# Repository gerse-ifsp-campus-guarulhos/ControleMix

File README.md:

# **ControleMix**

O Controle Mix é uma placa dedicada para a construção, desenvolvimento e prototipagem de robôs autônomos ou controlado, o foco dela é para robôs voltados a competição (mas isso não impede que a mesma seja usada em outros robôs ou em outras aplicações )

## **Circuito**
 
O circuito leva o [STM32F103C8T6](https://www.st.com/content/ccc/resource/technical/document/reference_manual/59/b9/ba/7f/11/af/43/d5/CD00171190.pdf/files/CD00171190.pdf/jcr:content/translations/en.CD00171190.pdf
) na plataforma  [Blue pill](https://www.techshopbd.com/uploads/product_document/STM32bluepillarduinoguide(1).pdf) a mesma dispõe de entradas e saídas e interfaces de comunicação serial , a ideia principal é universalizar os projetos e principalmente facilitar o projeto elétrico de forma que o desenvolvimento seja mais voltado para a programação. O circuito foi desenvolvido no Kicad e está projetado para fabricação manufatura ([consulte o GERBER](./DOC/GERBER/)), Para mais informações da placa consulte o [esquema elétrico](./DOC/ControleMix.pdf), O circuito contém:

* 10 entradas analogicas de 12 bits com divisor de tensão - 0V a 30V

* 4 saídas acoplada por um [ULN2803A](https://www.st.com/en/interfaces-and-transceivers/uln2803a.html)   (todas PWM)

* 4 Entradas acoplada por um  [ULN2803A](https://www.st.com/en/interfaces-and-transceivers/uln2803a.html)   (todas PWM)

* Serial USART1

* Serial USART3 / I2C2

* Serial USB / CAN

* Conector para mix de sinal do controle RF de até 6 canais

## **Notas para instalação e manipulação nos projetos:**

* sempre consulte o [esquema elétrico](./DOC/ControleMix.pdf).

* Ela tem aproximadamente 60mm por 60mm e contém 2 furos de fixação excêntrico e assimétricos.

* Aconselha se a utilizar de forma que o circuito não fique exposto, ela é utiliza  conectores [molex de passo 1.27mm](
https://www.molex.com/molex/news/display_news.jsp?channel=New&channelId=0&oid=941
)

* Os resistores do divisor de divisão de tensão e os resistores de pull up são array de resistores embora pode ser facilmente substituídos por resistores comuns

* Para desenho do projeto em [3D](./DOC/3D/) consulte o D do circuito

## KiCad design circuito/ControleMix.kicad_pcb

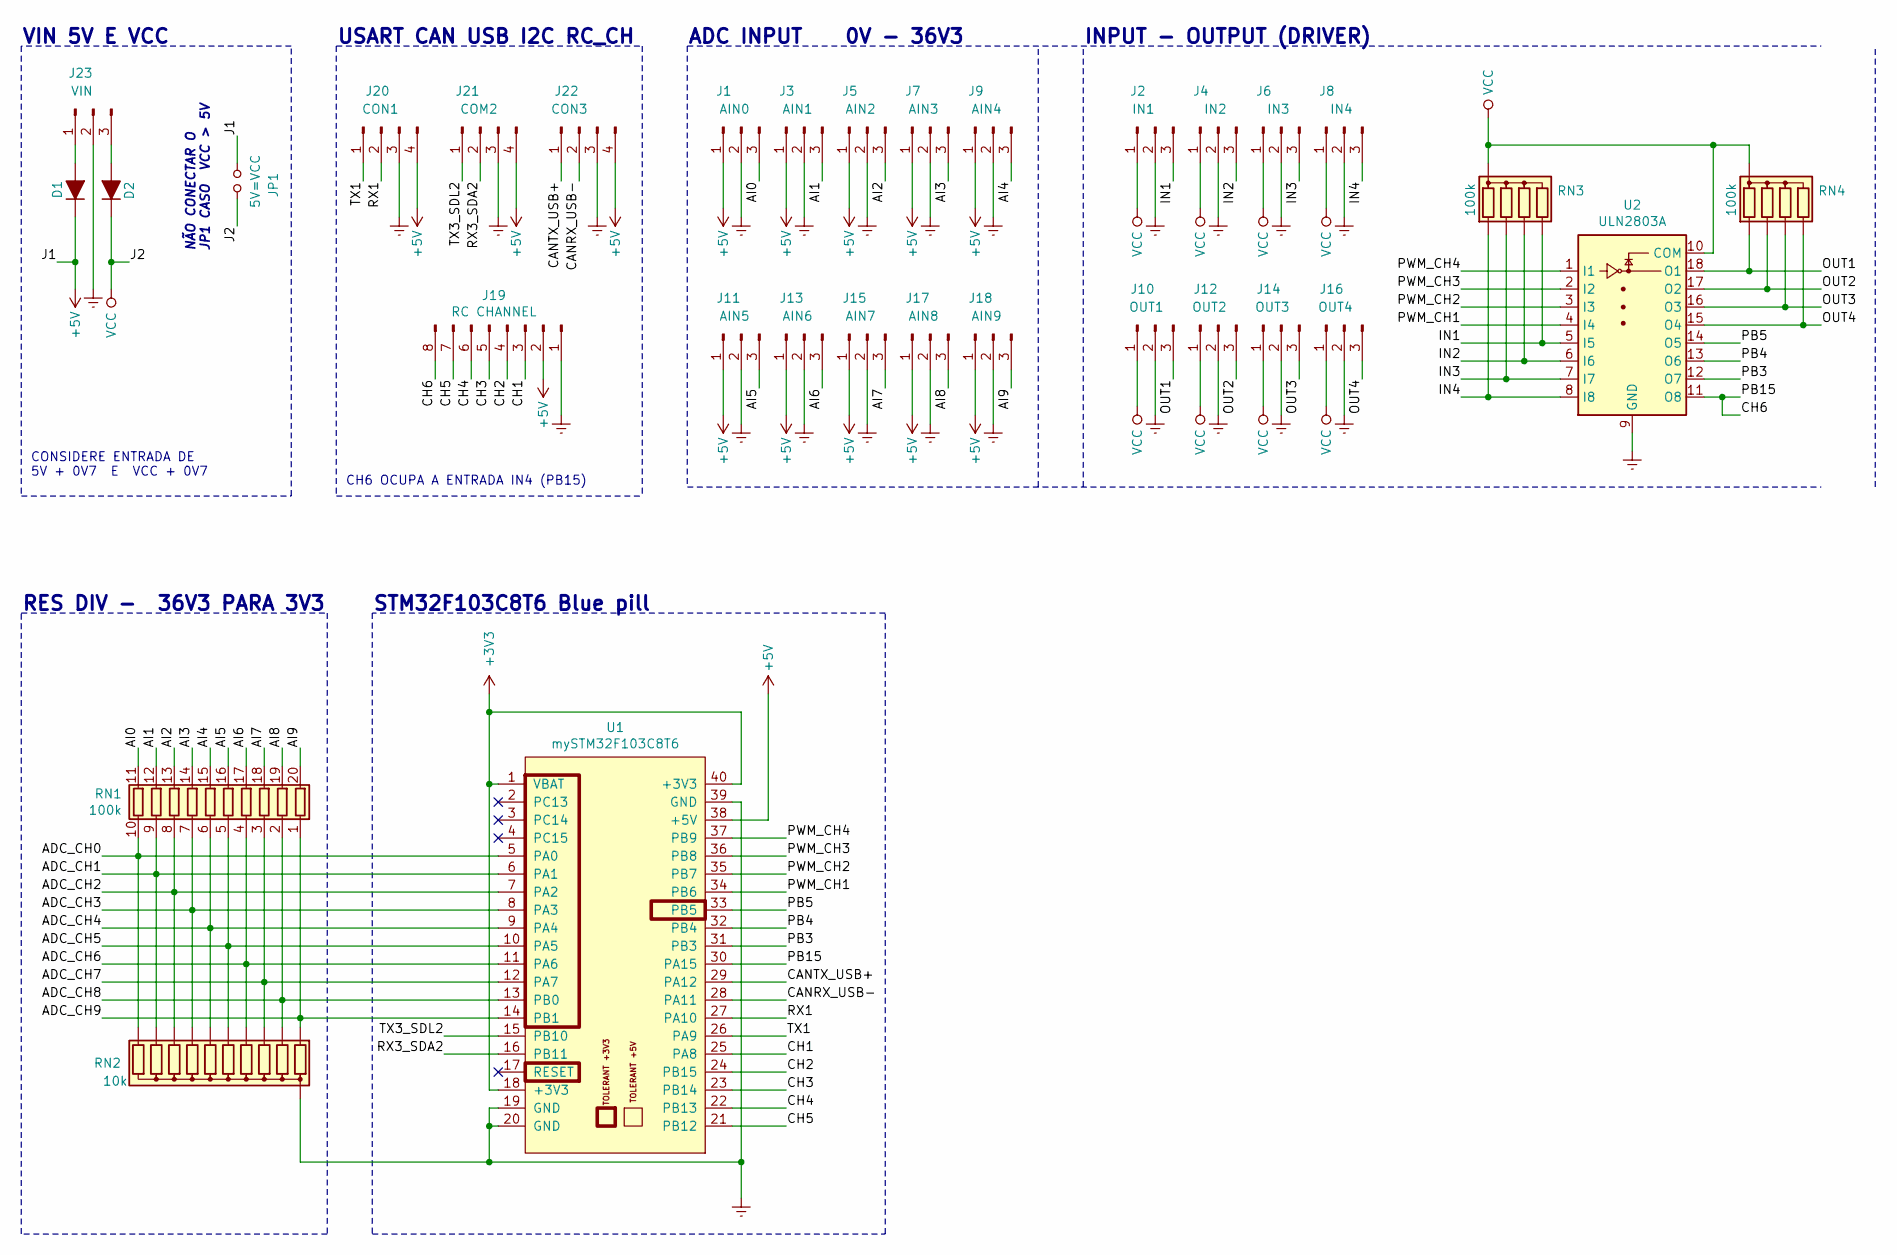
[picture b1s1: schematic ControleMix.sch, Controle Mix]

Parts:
D1, D2: D_ALT; D_MELF_Handsoldering
J1: AIN0; Molex_PicoBlade_53047-0310_1x03_P1.25mm_Vertical
J2: IN1; Molex_PicoBlade_53047-0310_1x03_P1.25mm_Vertical
J3: AIN1; Molex_PicoBlade_53047-0310_1x03_P1.25mm_Vertical
J4: IN2; Molex_PicoBlade_53047-0310_1x03_P1.25mm_Vertical
J5: AIN2; Molex_PicoBlade_53047-0310_1x03_P1.25mm_Vertical
J6: IN3; Molex_PicoBlade_53047-0310_1x03_P1.25mm_Vertical
J7: AIN3; Molex_PicoBlade_53047-0310_1x03_P1.25mm_Vertical
J8: IN4; Molex_PicoBlade_53047-0310_1x03_P1.25mm_Vertical
J9: AIN4; Molex_PicoBlade_53047-0310_1x03_P1.25mm_Vertical
J10: OUT1; Molex_PicoBlade_53047-0310_1x03_P1.25mm_Vertical
J11: AIN5; Molex_PicoBlade_53047-0310_1x03_P1.25mm_Vertical
J12: OUT2; Molex_PicoBlade_53047-0310_1x03_P1.25mm_Vertical
J13: AIN6; Molex_PicoBlade_53047-0310_1x03_P1.25mm_Vertical
J14: OUT3; Molex_PicoBlade_53047-0310_1x03_P1.25mm_Vertical
J15: AIN7; Molex_PicoBlade_53047-0310_1x03_P1.25mm_Vertical
J16: OUT4; Molex_PicoBlade_53047-0310_1x03_P1.25mm_Vertical
J17: AIN8; Molex_PicoBlade_53047-0310_1x03_P1.25mm_Vertical
J18: AIN9; Molex_PicoBlade_53047-0310_1x03_P1.25mm_Vertical
J19: RC CHANNEL; Molex_PicoBlade_53047-0810_1x08_P1.25mm_Vertical
J20: CON1; Molex_PicoBlade_53047-0410_1x04_P1.25mm_Vertical
J21: COM2; Molex_PicoBlade_53047-0410_1x04_P1.25mm_Vertical
J22: CON3; Molex_PicoBlade_53047-0410_1x04_P1.25mm_Vertical
J23: VIN; Molex_PicoBlade_53047-0310_1x03_P1.25mm_Vertical
JP1: 5V=VCC; PinSocket_1x02_P2.54mm_Vertical
RN1: 100k; DIP-20_W7.62mm
RN2: 10k; R_Array_SIP11
RN3, RN4: 100k; R_Array_SIP5
U1: mySTM32F103C8T6; stm32f103c8t6-module-china
U2: ULN2803A; SOIC-18W_7.5x11.6mm_P1.27mm

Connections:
+3V3: U1.1 (VBAT), U1.18 (+3V3), U1.40 (+3V3)
+5V: D1.1 (K), J1.1, J3.1, J5.1, J7.1, J9.1, J11.1, J13.1, J15.1, J17.1, J18.1, J19.2, J20.4, J21.4, J22.4, JP1.1, U1.38 (+5V)
/ADC_CH0: RN1.10 (R10.1), RN2.11 (R10), U1.5 (PA0)
/ADC_CH1: RN1.9 (R9.1), RN2.10 (R9), U1.6 (PA1)
/ADC_CH2: RN1.8 (R8.1), RN2.9 (R8), U1.7 (PA2)
/ADC_CH3: RN1.7 (R7.1), RN2.8 (R7), U1.8 (PA3)
/ADC_CH4: RN1.6 (R6.1), RN2.7 (R6), U1.9 (PA4)
/ADC_CH5: RN1.5 (R5.1), RN2.6 (R5), U1.10 (PA5)
/ADC_CH6: RN1.4 (R4.1), RN2.5 (R4), U1.11 (PA6)
/ADC_CH7: RN1.3 (R3.1), RN2.4 (R3), U1.12 (PA7)
/ADC_CH8: RN1.2 (R2.1), RN2.3 (R2), U1.13 (PB0)
/ADC_CH9: RN1.1 (R1.1), RN2.2 (R1), U1.14 (PB1)
/AI0: J1.3, RN1.11 (R10.2)
/AI1: J3.3, RN1.12 (R9.2)
/AI2: J5.3, RN1.13 (R8.2)
/AI3: J7.3, RN1.14 (R7.2)
/AI4: J9.3, RN1.15 (R6.2)
/AI5: J11.3, RN1.16 (R5.2)
/AI6: J13.3, RN1.17 (R4.2)
/AI7: J15.3, RN1.18 (R3.2)
/AI8: J17.3, RN1.19 (R2.2)
/AI9: J18.3, RN1.20 (R1.2)
/CANRX_USB-: J22.2, U1.28 (PA11)
/CANTX_USB+: J22.1, U1.29 (PA12)
/CH1: J19.3, U1.25 (PA8)
/CH2: J19.4, U1.24 (PB15)
/CH3: J19.5, U1.23 (PB14)
/CH4: J19.6, U1.22 (PB13)
/CH5: J19.7, U1.21 (PB12)
/CH6: J19.8, U1.30 (PA15), U2.11 (O8)
/IN1: J2.3, RN3.5 (R4), U2.5 (I5)
/IN2: J4.3, RN3.4 (R3), U2.6 (I6)
/IN3: J6.3, RN3.3 (R2), U2.7 (I7)
/IN4: J8.3, RN3.2 (R1), U2.8 (I8)
/OUT1: J10.3, RN4.2 (R1), U2.18 (O1)
/OUT2: J12.3, RN4.3 (R2), U2.17 (O2)
/OUT3: J14.3, RN4.4 (R3), U2.16 (O3)
/OUT4: J16.3, RN4.5 (R4), U2.15 (O4)
/PB3: U1.31 (PB3), U2.12 (O7)
/PB4: U1.32 (PB4), U2.13 (O6)
/PB5: U1.33 (PB5), U2.14 (O5)
/PWM_CH1: U1.34 (PB6), U2.4 (I4)
/PWM_CH2: U1.35 (PB7), U2.3 (I3)
/PWM_CH3: U1.36 (PB8), U2.2 (I2)
/PWM_CH4: U1.37 (PB9), U2.1 (I1)
/RX1: J20.2, U1.27 (PA10)
/RX3_SDA2: J21.2, U1.16 (PB11)
/TX1: J20.1, U1.26 (PA9)
/TX3_SDL2: J21.1, U1.15 (PB10)
Earth: J1.2, J2.2, J3.2, J4.2, J5.2, J6.2, J7.2, J8.2, J9.2, J10.2, J11.2, J12.2, J13.2, J14.2, J15.2, J16.2, J17.2, J18.2, J19.1, J20.3, J21.3, J22.3, J23.2, RN2.1 (common), U1.19 (GND), U1.20 (GND), U1.39 (GND), U2.9 (GND)
unnamed: D1.2 (A), J23.1
unnamed: D2.2 (A), J23.3
VCC: D2.1 (K), J2.1, J4.1, J6.1, J8.1, J10.1, J12.1, J14.1, J16.1, JP1.2, RN3.1 (common), RN4.1 (common), U2.10 (COM)

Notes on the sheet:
INPUT - OUTPUT (DRIVER)
ADC INPUT 0V - 36V3
VIN 5V E VCC
NÃO CONECTAR O JP1 CASO VCC > 5V
USART CAN USB I2C RC_CH
RES DIV - 36V3 PARA 3V3
CONSIDERE ENTRADA DE 5V + 0V7 E VCC + 0V7
CH6 OCUPA A ENTRADA IN4 (PB15)
STM32F103C8T6 Blue pill

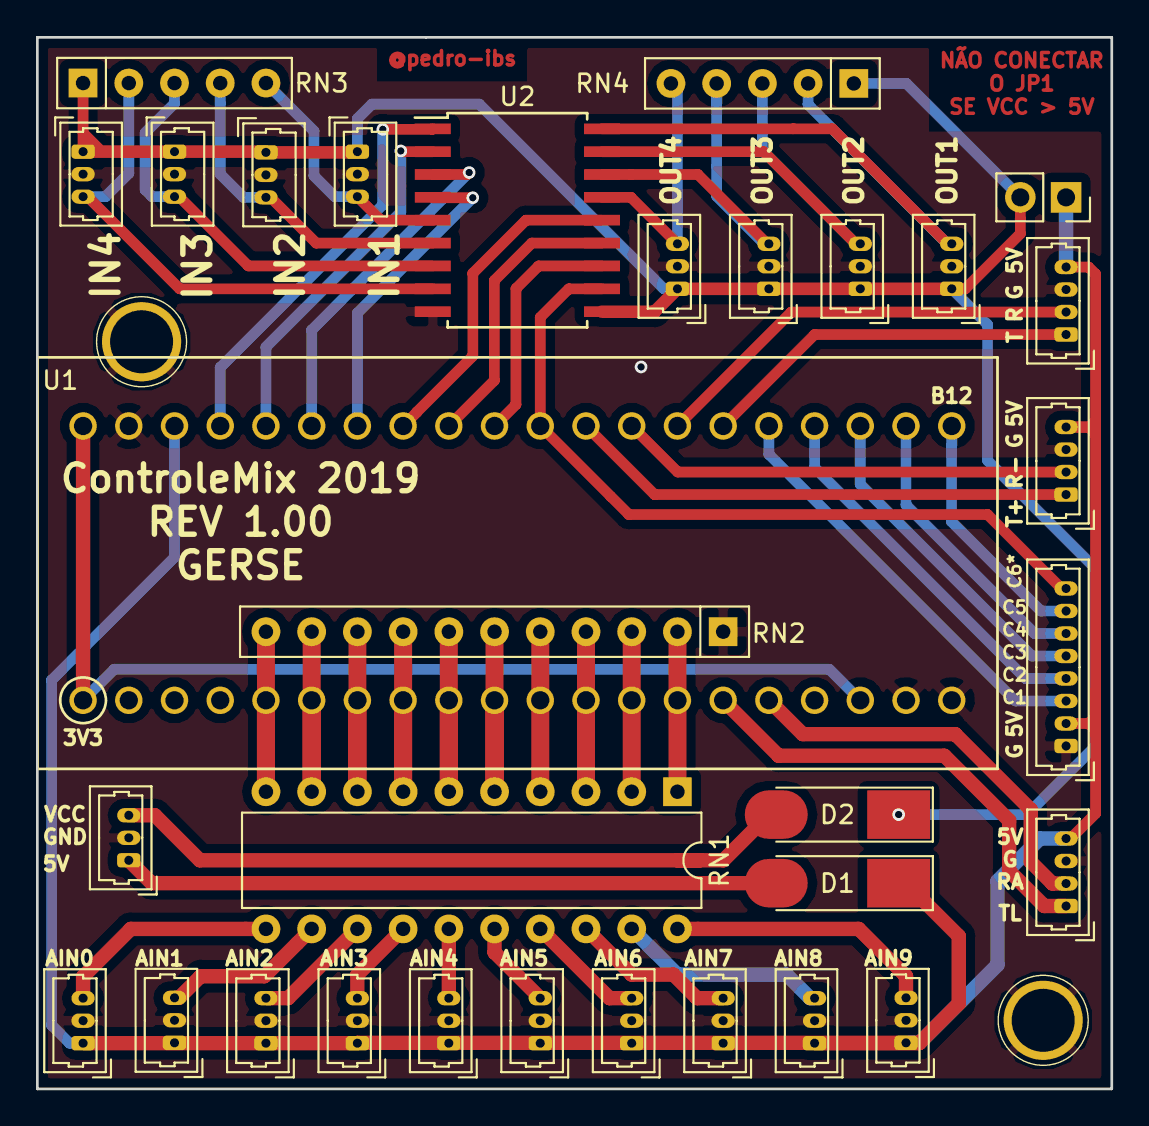
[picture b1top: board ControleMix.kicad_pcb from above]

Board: 2 copper layers, 59.7 x 58.4 mm, 32 parts (0 on the bottom side), 53 nets.

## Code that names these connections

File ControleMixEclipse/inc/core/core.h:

/*
 * config.h
 *
 *  Created on: 27 de set de 2019
 *      Author: pibs
 */

#include <sysBase/gpio.h>
#include <sysBase/pwm.h>
#include <sysBase/adc.h>
#include <sysBase/usartx.h>
#include <core/protocol.h>
#include <core/dbg.h>
#include <core/chMix.h>


#ifndef CONFIG_H_
#define CONFIG_H_

// config da comunicação serial e DBG
#define DEC			10		// base 10, conversão str -> int do dbg
#define BAUDRATE		19200		// velocidade
#define USART_DBG		USART1		// periferio
#define SERIAL			USART_DBG	// tradução


// config de inicialização do timer e rtc
#define MINIMAL_TIME_MS		1		// tempo minimo do millis()
#define INIT_CONTER		0		// iniciar contagem do milles em zero

// lede do pill blue
#define LED			GPIOC13		//
#define TIME_BLK		200		// tempo em miles segundos para piscadas do les 13


// entrada drvere
#define IN1 			GPIOB5
#define IN2 			GPIOB4
#define IN3 			GPIOB3
#define IN4 			GPIOA15		// TB É CH6

// saidas driver e PWM
#define OUT1 			PWM_CH4
#define OUT2 			PWM_CH3
#define OUT3 			PWM_CH2
#define OUT4 			PWM_CH1

// adc
#define AIN0			ADC_CH0
#define AIN1			ADC_CH1
#define AIN2			ADC_CH2
#define AIN3			ADC_CH3
#define AIN4			ADC_CH4
#define AIN5			ADC_CH5
#define AIN6			ADC_CH6
#define AIN7			ADC_CH7
#define AIN8			ADC_CH8
#define AIN9			ADC_CH9

// entrada do controle RS
#define CH1			GPIOA8
#define CH2			GPIOB15
#define CH3			GPIOB14
#define CH4			GPIOB13
#define CH5			GPIOB12
#define CH6			GPIOA15		// TB É IN4


void coreInit(void);
void blkLed(void);
void coreMonitor(void);
bool initIsOK(void);

#endif /* CONFIG_H_ */

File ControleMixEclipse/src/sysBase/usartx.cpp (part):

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		GPIO_PinRemapConfig(GPIO_Remap_USART1,	ENABLE);
	}

	/* Configure PB7 and PB6 as USART1 TX/RX */
	/* PB6 = alternate function push/pull output */

	GPIO_InitTypeDef gpio;
	gpio.GPIO_Pin			= RemapPin?GPIO_Pin_6:GPIO_Pin_9;	// TX pin
	gpio.GPIO_Speed			= GPIO_Speed_50MHz;			// speed pin
	gpio.GPIO_Mode			= GPIO_Mode_AF_PP;			// push up
	GPIO_Init(GPIOA, &gpio);
	/* PB7 = floating input */
	gpio.GPIO_Pin			= RemapPin?GPIO_Pin_7:GPIO_Pin_10;	// RX pin
	gpio.GPIO_Mode			= GPIO_Mode_IN_FLOATING;		// ploating point
	GPIO_Init((RemapPin?GPIOB:GPIOA), &gpio);
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	RCC_APB2PeriphClockCmd(RCC_APB2Periph_GPIOA,	ENABLE);
	RCC_APB2PeriphClockCmd(RCC_APB2Periph_AFIO,	ENABLE);

	/* Configure PA9 and PA10 as USART1 TX/RX */
	/* PA9 = alternate function push/pull output */
	GPIO_InitTypeDef gpio;
	gpio.GPIO_Pin			= GPIO_Pin_2;				// TX pin
	gpio.GPIO_Speed			= GPIO_Speed_50MHz;			// speed pin
	gpio.GPIO_Mode			= GPIO_Mode_AF_PP;			// push up
	GPIO_Init(GPIOA, &gpio);
	/* PA10 = floating input */
	gpio.GPIO_Pin			= GPIO_Pin_3;				// RX pin
	gpio.GPIO_Mode			= GPIO_Mode_IN_FLOATING;		// ploating point
	GPIO_Init(GPIOA, &gpio);
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	RCC_APB2PeriphClockCmd(RCC_APB2Periph_GPIOB,	ENABLE);
	RCC_APB2PeriphClockCmd(RCC_APB2Periph_AFIO,	ENABLE);

	/* Configure PA9 and PA10 as USART1 TX/RX */
	/* PA9 = alternate function push/pull output */
	GPIO_InitTypeDef gpio;
	gpio.GPIO_Pin			= GPIO_Pin_10;				// TX pin
	gpio.GPIO_Speed			= GPIO_Speed_50MHz;			// speed pin
	gpio.GPIO_Mode			= GPIO_Mode_AF_PP;			// push up
	GPIO_Init(GPIOB, &gpio);
	/* PA10 = floating input */
	gpio.GPIO_Pin			= GPIO_Pin_11;				// RX pin
	gpio.GPIO_Mode			= GPIO_Mode_IN_FLOATING;		// ploating point
	GPIO_Init(GPIOB, &gpio);
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
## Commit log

2019-09-26 new rep fcm
2019-09-26 arrumando Redame
2019-09-26 att redame
2019-09-26 arrumando esquema
2019-10-01 code

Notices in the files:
ControleMixEclipse/src/sysBase/usartx.cpp:
Copyright (C) Pedro Igor B. S 2018
Licença: GNU GPL 2
modify it under the terms of the GNU General Public License as
published by the Free Software Foundation; version 2 of the
License.
